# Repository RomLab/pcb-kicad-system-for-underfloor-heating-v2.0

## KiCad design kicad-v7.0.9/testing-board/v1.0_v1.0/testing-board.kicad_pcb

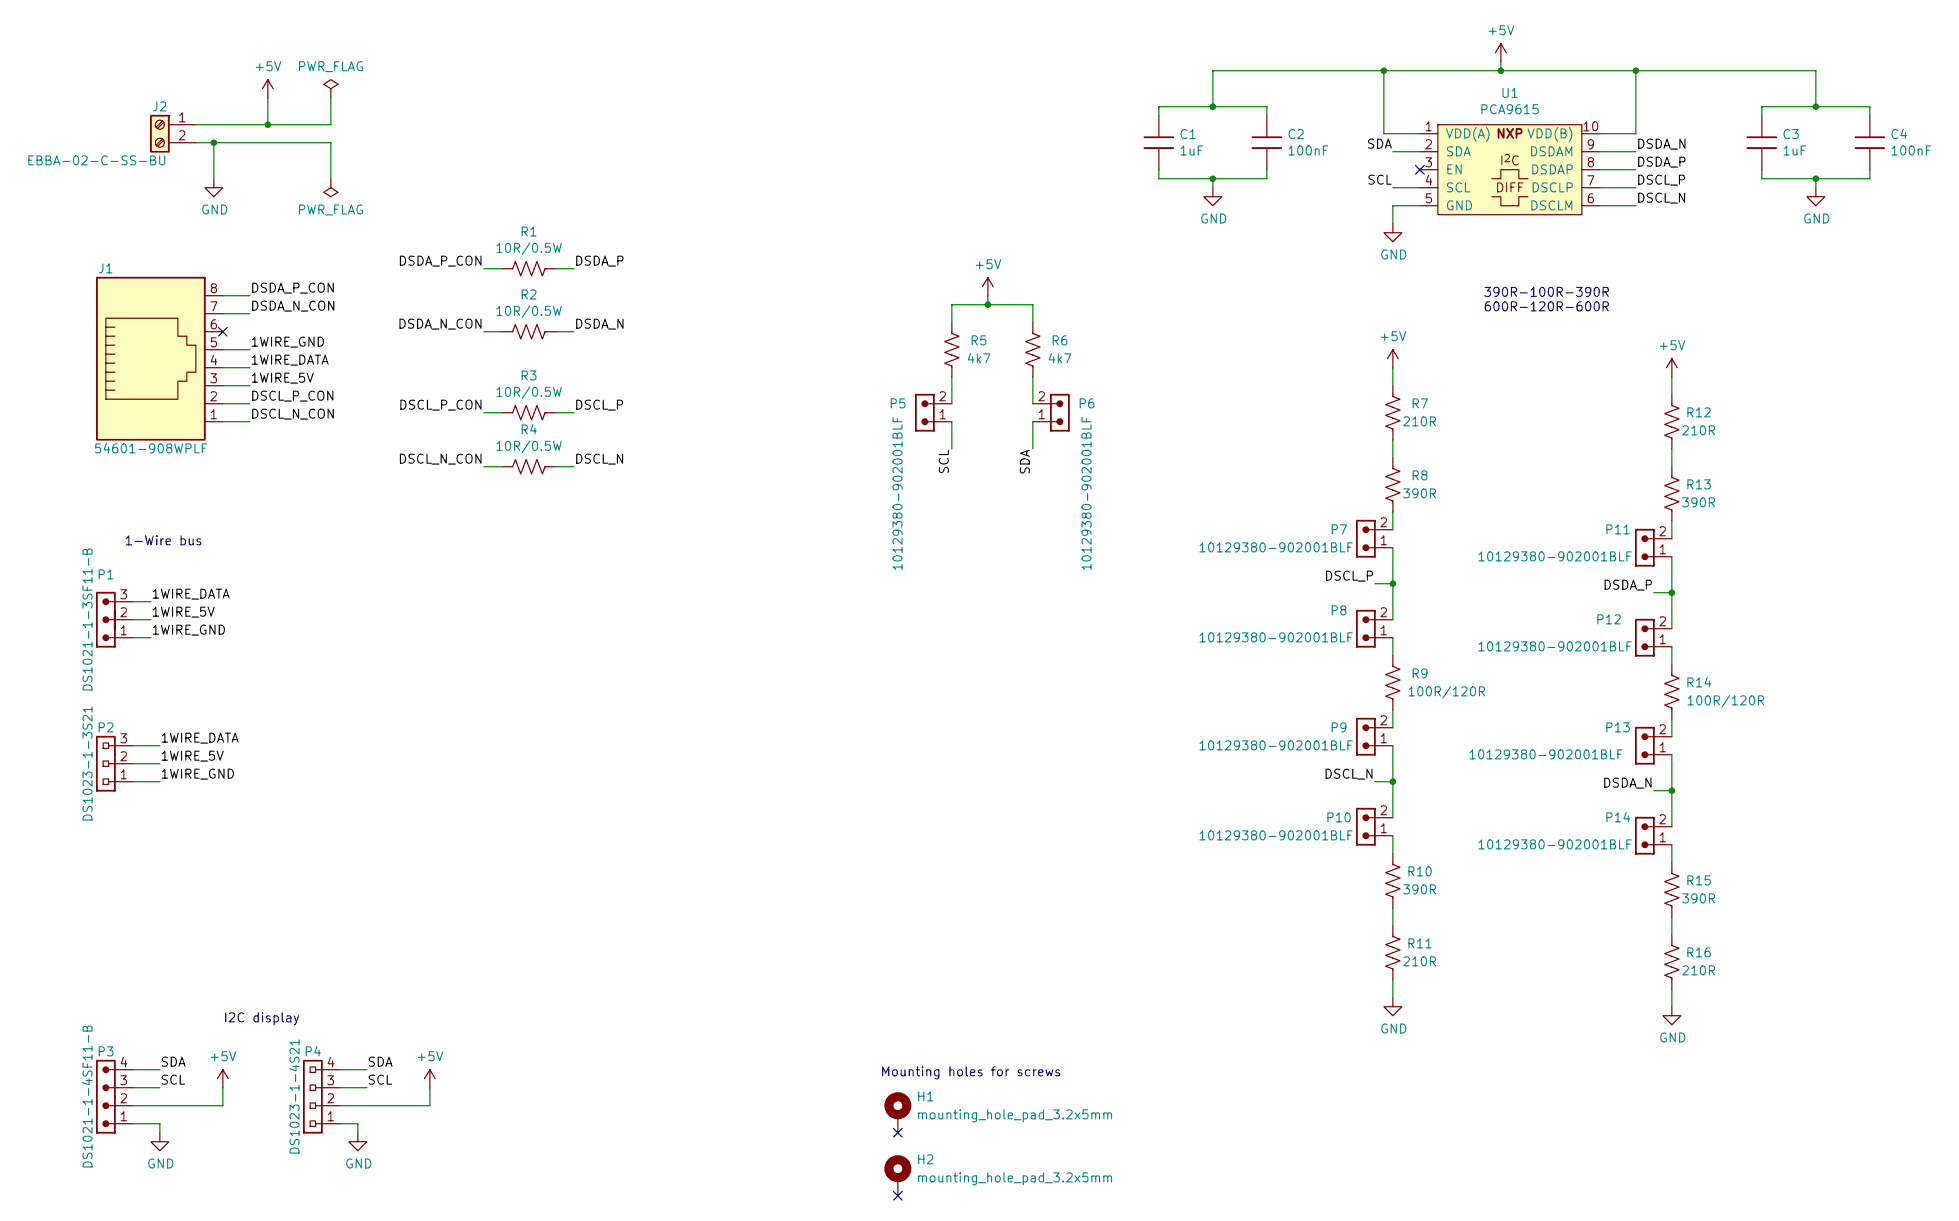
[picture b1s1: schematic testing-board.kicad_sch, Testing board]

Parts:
C1, C3: 1uF; c_1206
C2, C4: 100nF; c_1206
H1, H2: mounting_hole_pad_3.2x5mm
J1: 54601-908WPLF; rj45_54601-908WPLF
J2: EBBA-02-C-SS-BU
P1: DS1021-1-3SF11-B; 1x3_pinheader_2.54mm_vertical
P2: DS1023-1-3S21; 1x3_pinsocket_2.54mm_vertical_8.4mm
P3: DS1021-1-4SF11-B; 1x4_pinheader_2.54mm_vertical
P4: DS1023-1-4S21; 1x4_pinsocket_2.54mm_vertical_8.4mm
P5, P6, P7, P8, P9, P10, P11, P12, P13, P14: 10129380-902001BLF; 1x2_pinheader_2.54mm_vertical
R1, R2, R3, R4: 10R/0.5W; r_1206
R5, R6: 4k7; r_1206
R7, R11, R12, R16: 210R; r_1206
R8, R10, R13, R15: 390R; r_1206
R9, R14: 100R/120R; r_1206
U1: PCA9615; tssop_10

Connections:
+5V: C1.1, C2.1, C3.1, C4.1, J2.1, P3.2, P4.2, R5.1, R6.1, R7.1, R12.1, U1.1 (VDD(A)), U1.10 (VDD(B))
/1WIRE_5V: J1.3, P1.2, P2.2
/1WIRE_DATA: J1.4, P1.3, P2.3
/1WIRE_GND: J1.5, P1.1, P2.1
/DSCL_N: P9.1, P10.2, R4.2, U1.6 (DSCLM)
/DSCL_N_CON: J1.1, R4.1
/DSCL_P: P7.1, P8.2, R3.2, U1.7 (DSCLP)
/DSCL_P_CON: J1.2, R3.1
/DSDA_N: P13.1, P14.2, R2.2, U1.9 (DSDAM)
/DSDA_N_CON: J1.7, R2.1
/DSDA_P: P11.1, P12.2, R1.2, U1.8 (DSDAP)
/DSDA_P_CON: J1.8, R1.1
/SCL: P3.3, P4.3, P5.1, U1.4 (SCL)
/SDA: P3.4, P4.4, P6.1, U1.2 (SDA)
GND: C1.2, C2.2, C3.2, C4.2, J2.2, P3.1, P4.1, R11.2, R16.2, U1.5 (GND)
unnamed: P5.2, R5.2
unnamed: P6.2, R6.2
unnamed: P7.2, R8.2
unnamed: P8.1, R9.1
unnamed: P9.2, R9.2
unnamed: P10.1, R10.1
unnamed: P11.2, R13.2
unnamed: P12.1, R14.1
unnamed: P13.2, R14.2
unnamed: P14.1, R15.1
unnamed: R7.2, R8.1
unnamed: R10.2, R11.1
unnamed: R12.2, R13.1
unnamed: R15.2, R16.1

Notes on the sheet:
1-Wire bus
Mounting holes for screws
I2C display
390R-100R-390R 600R-120R-600R

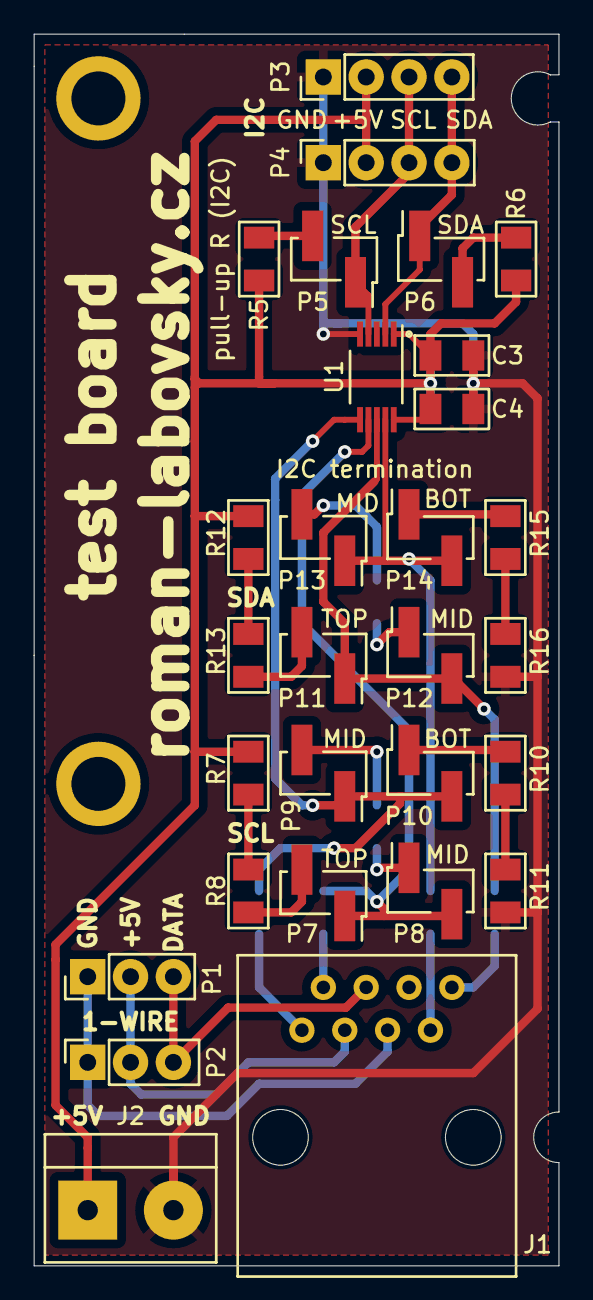
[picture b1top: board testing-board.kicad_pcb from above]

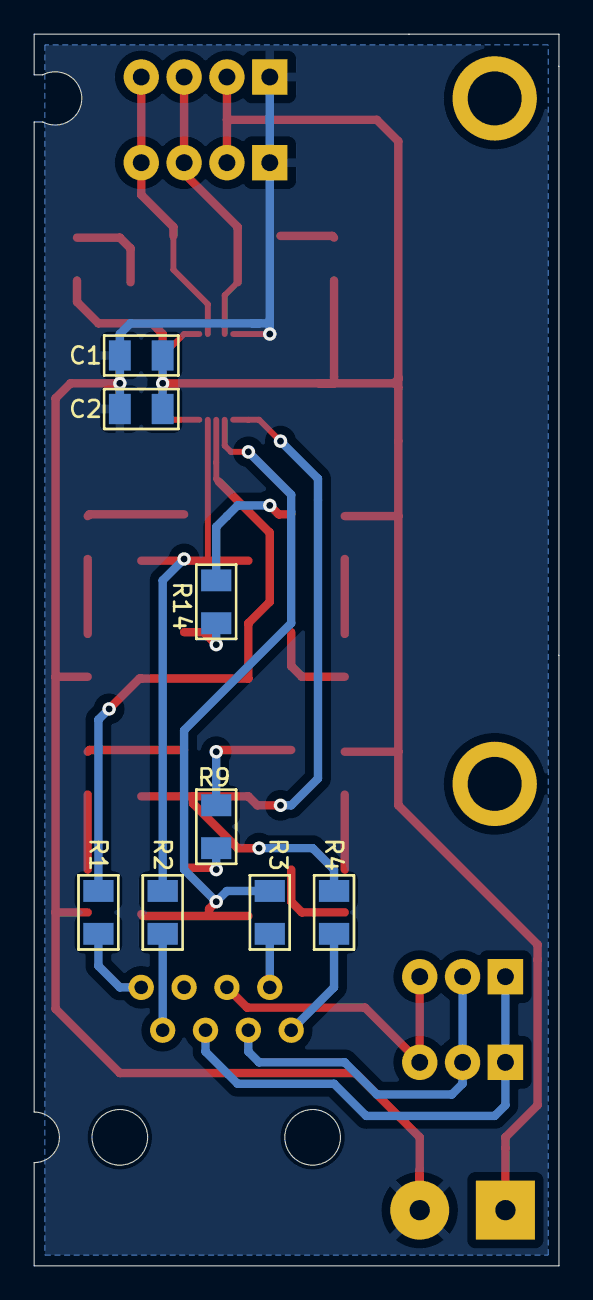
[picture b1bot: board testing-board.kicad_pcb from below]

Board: 2 copper layers, 31.1 x 73.0 mm, 39 parts (8 on the bottom side), 29 nets.

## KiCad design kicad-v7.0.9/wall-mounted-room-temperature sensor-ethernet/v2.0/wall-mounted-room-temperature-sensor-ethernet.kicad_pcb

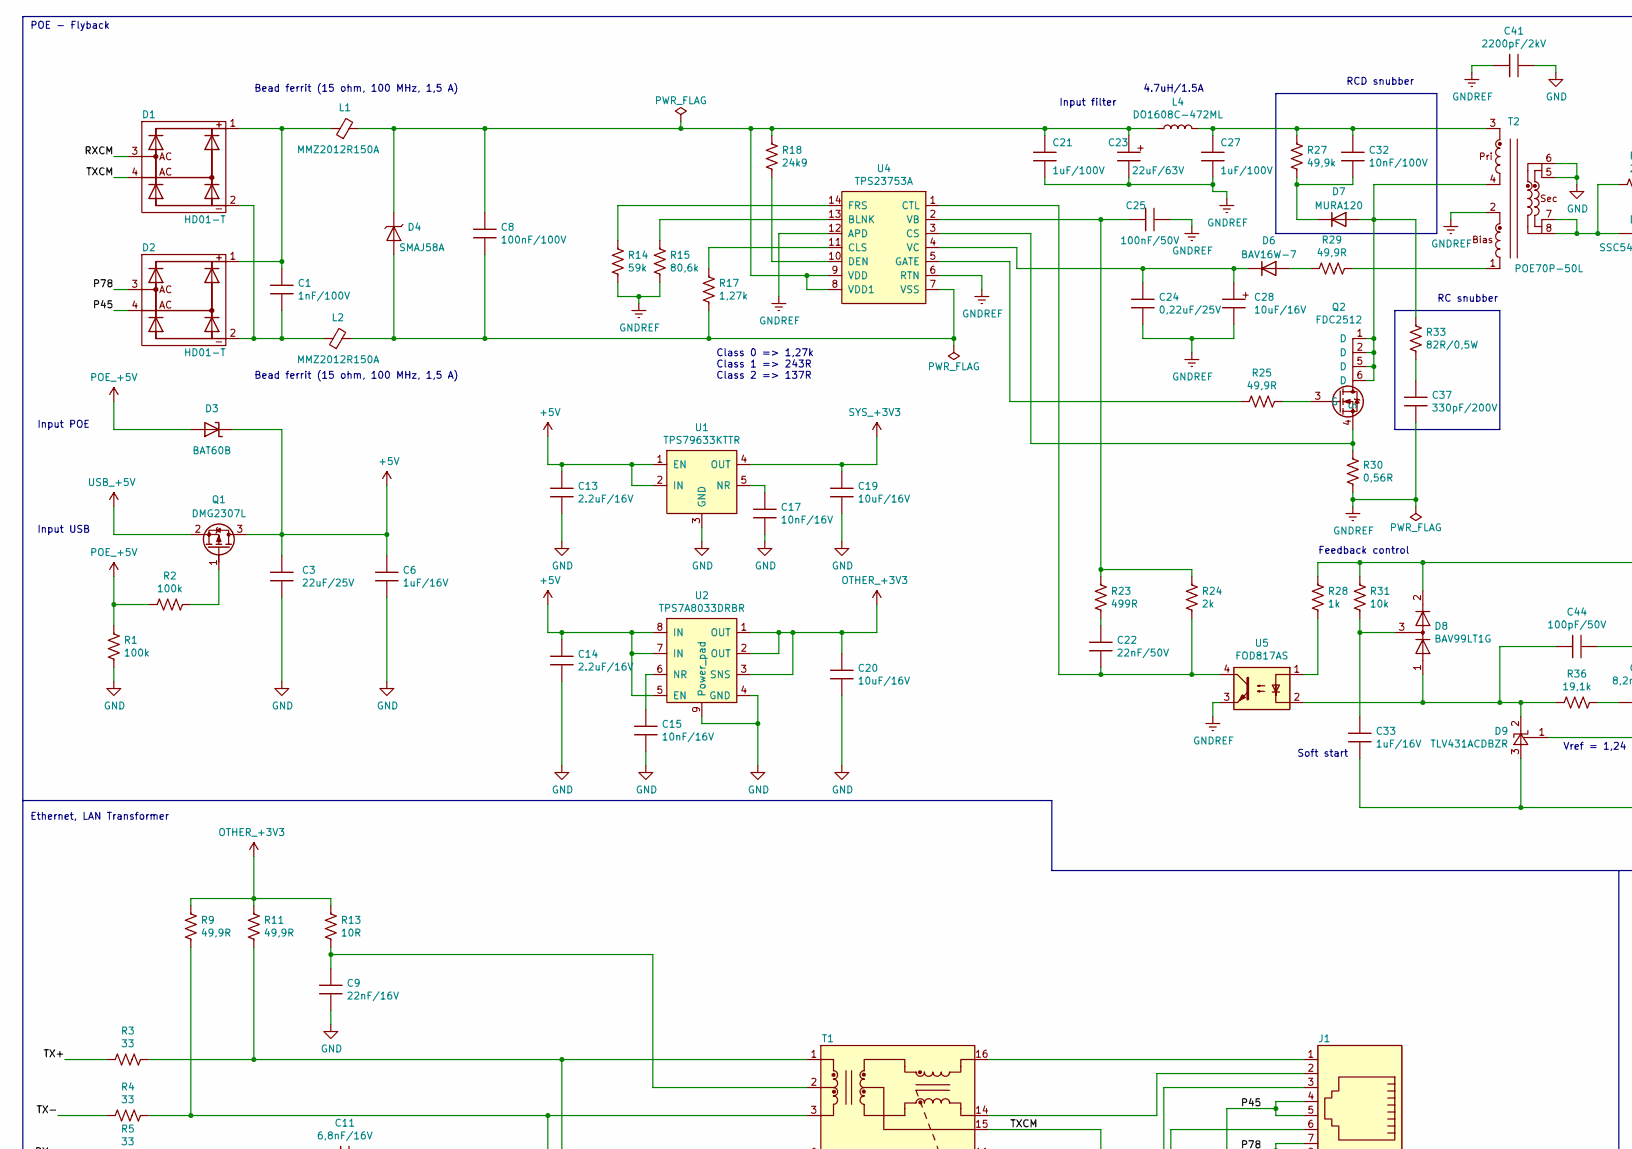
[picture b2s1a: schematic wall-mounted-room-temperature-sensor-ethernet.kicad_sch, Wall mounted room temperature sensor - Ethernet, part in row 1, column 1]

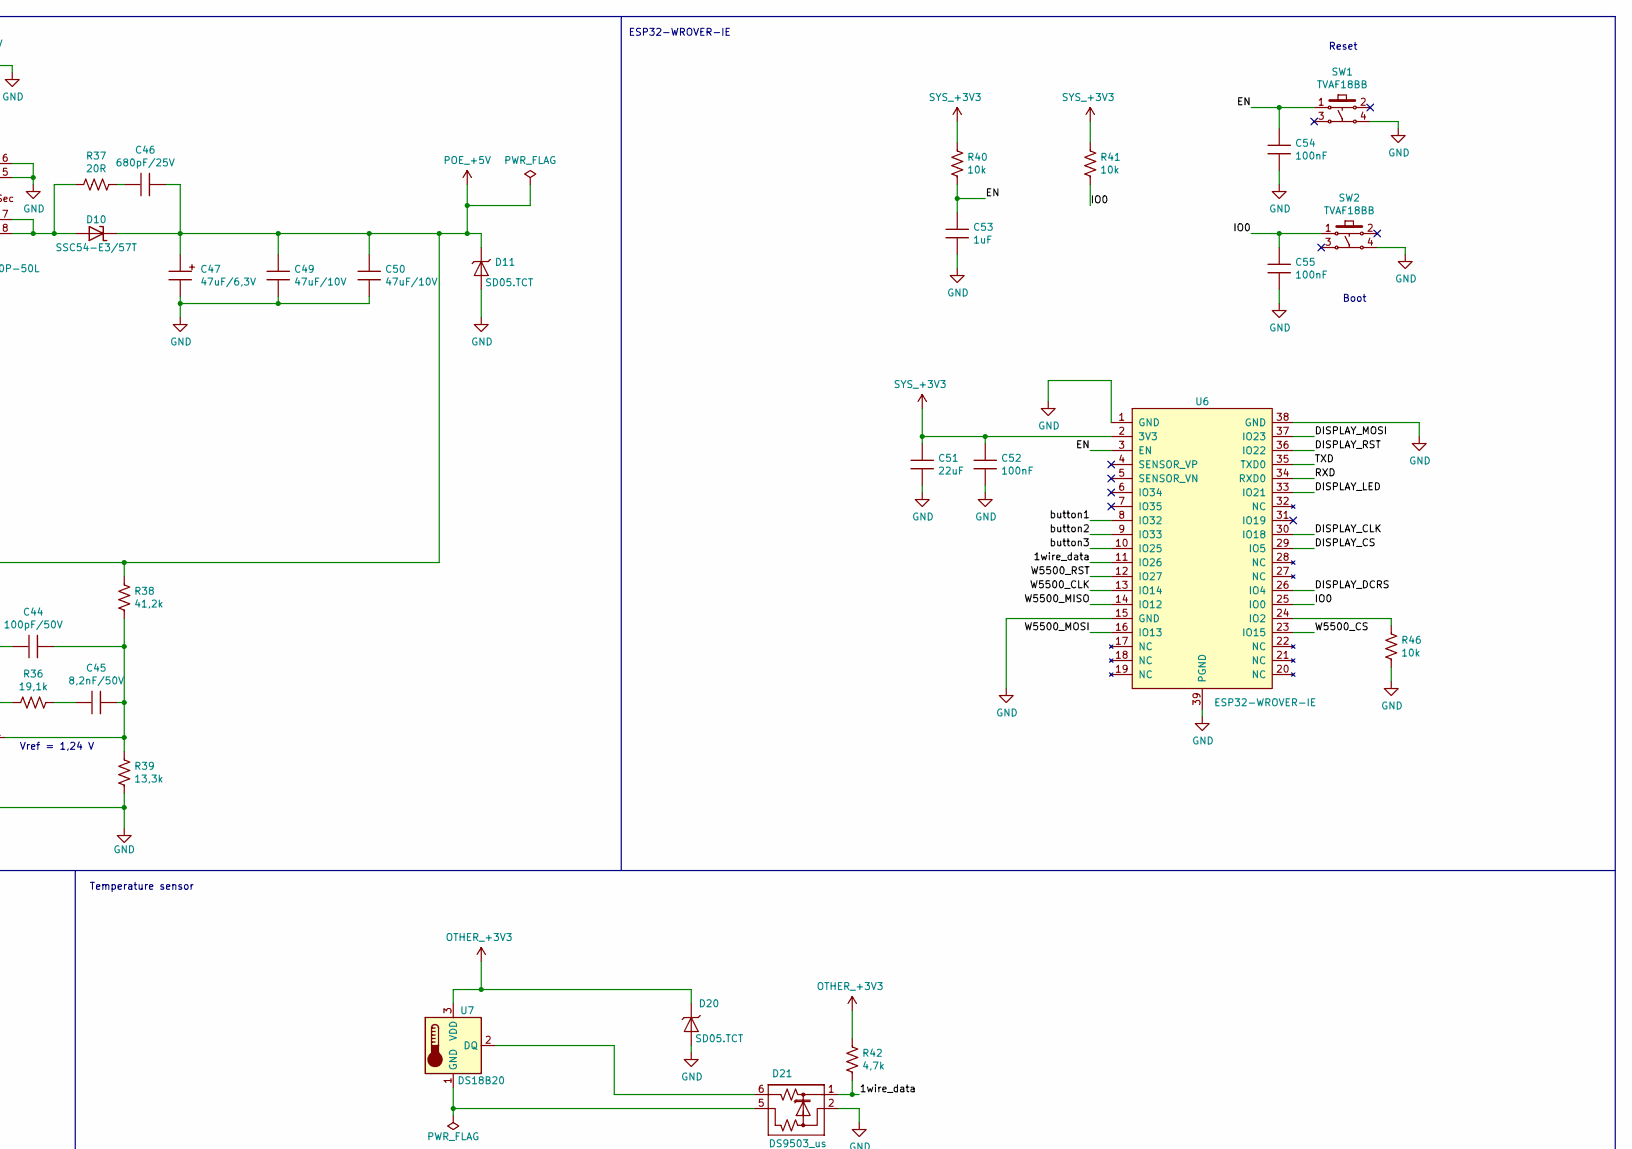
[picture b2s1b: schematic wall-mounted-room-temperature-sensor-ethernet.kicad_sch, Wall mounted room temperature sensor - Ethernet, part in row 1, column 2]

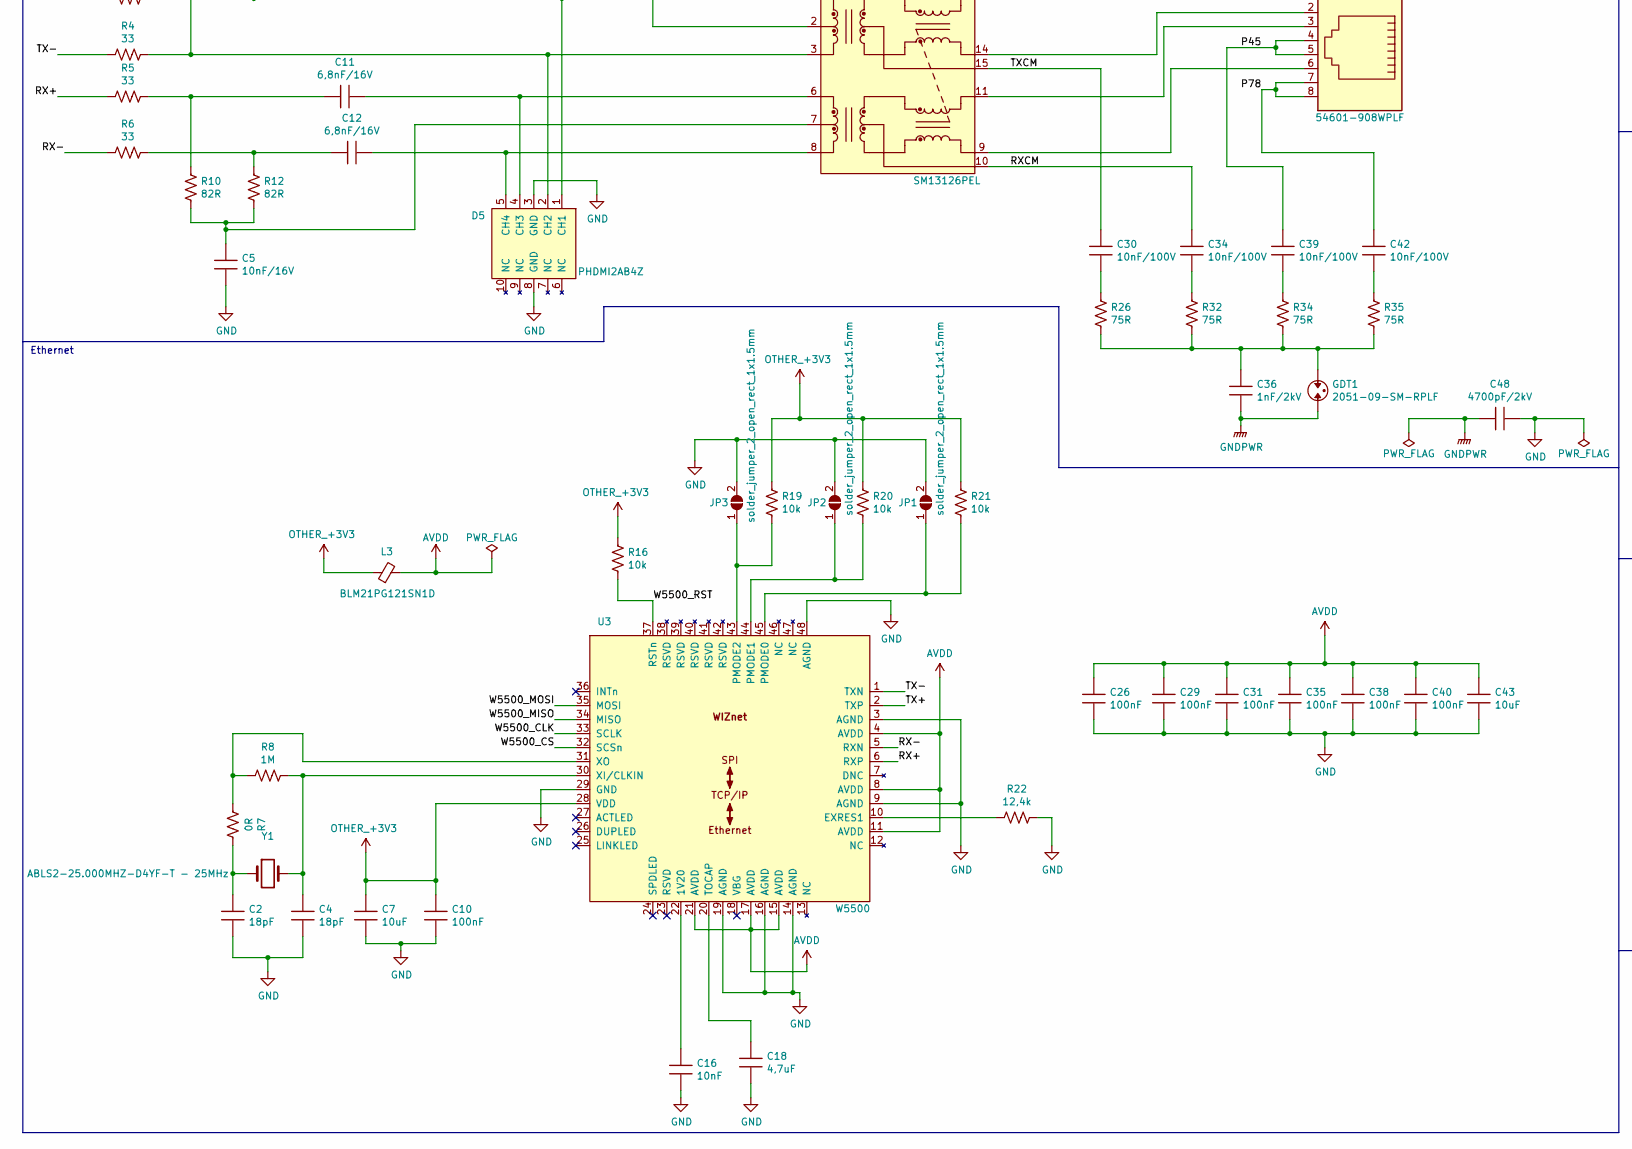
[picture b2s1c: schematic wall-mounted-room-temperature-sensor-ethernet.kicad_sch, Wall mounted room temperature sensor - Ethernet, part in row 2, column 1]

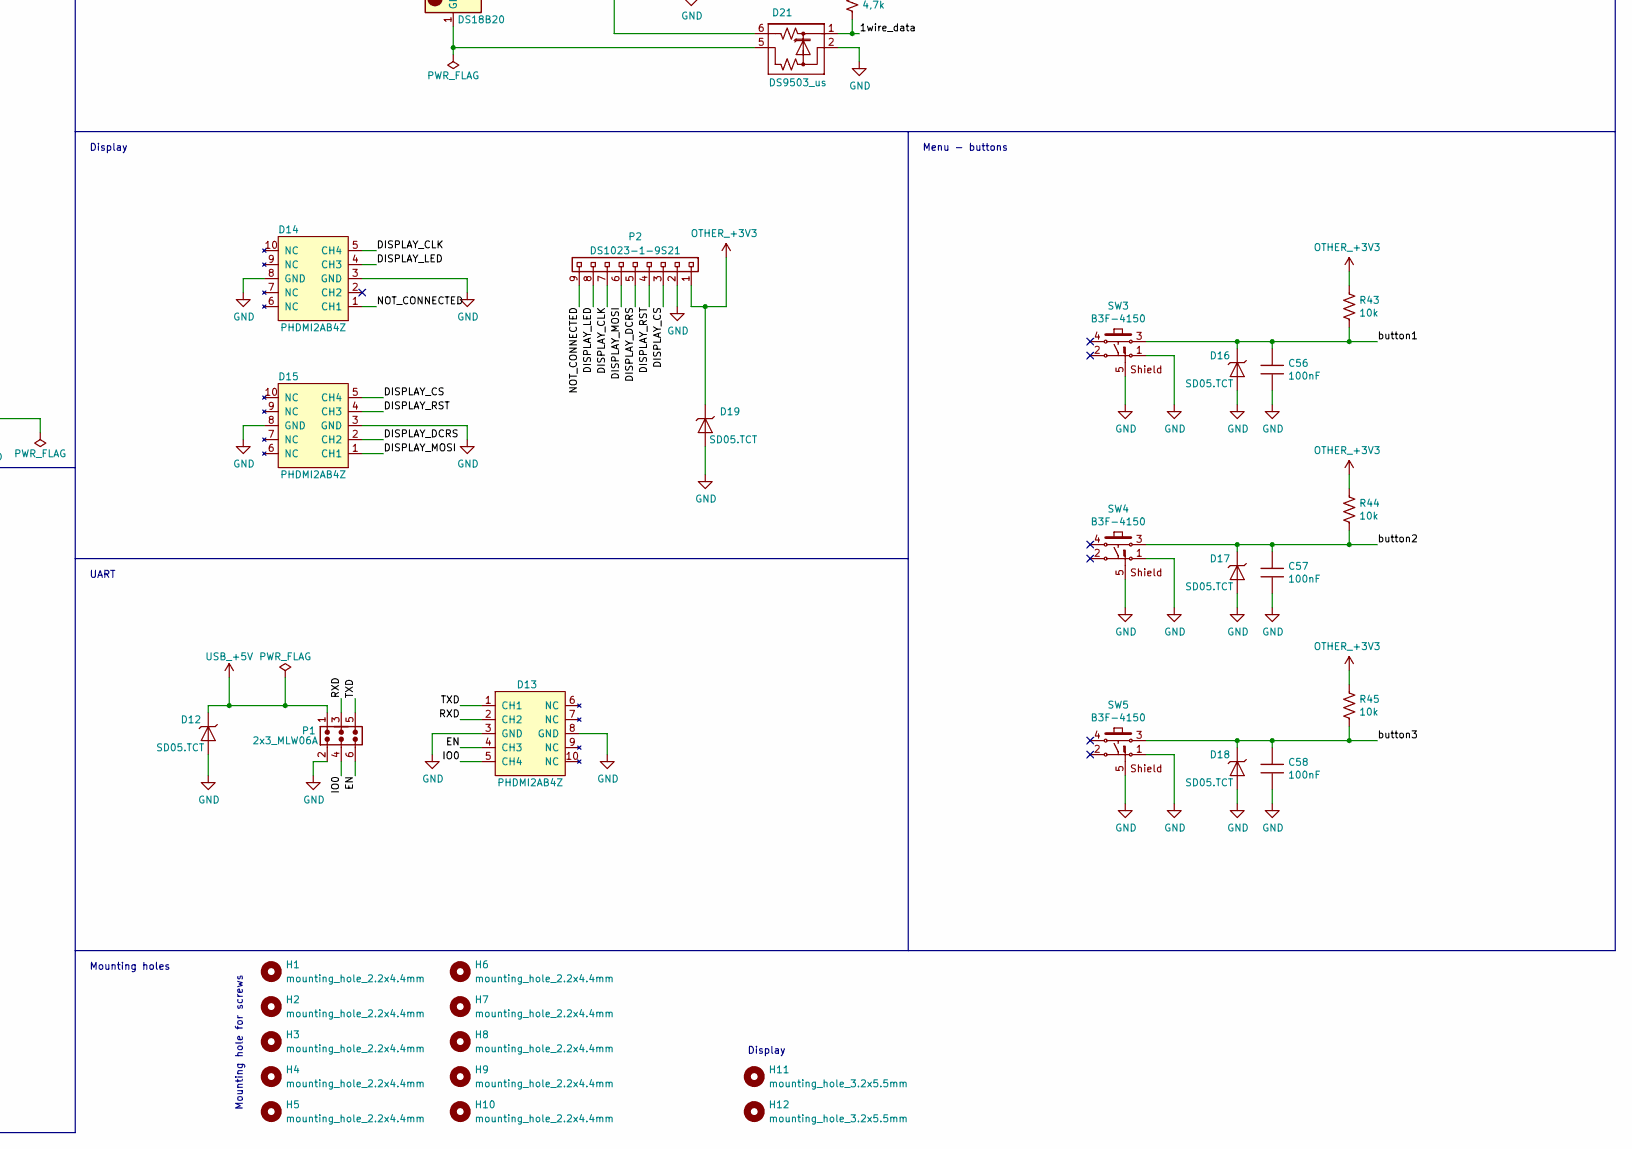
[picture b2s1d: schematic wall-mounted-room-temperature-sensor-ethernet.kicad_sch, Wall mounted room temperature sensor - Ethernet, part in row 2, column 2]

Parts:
C1: 1nF/100V; c_0805
C2, C4: 18pF; c_0805
C3: 22uF/25V; c_0805
C5, C15, C17: 10nF/16V; c_0805
C6, C33: 1uF/16V; c_0805
C7, C43: 10uF; c_0805
C8: 100nF/100V; c_0805
C9: 22nF/16V; c_0805
C10, C26, C29, C31, C35, C38, C40, C52, C54, C55, C56, C57, C58: 100nF; c_0805
C11, C12: 6,8nF/16V; c_0805
C13, C14: 2.2uF/16V; c_0805
C16: 10nF; c_0805
C18: 4,7uF; c_0805
C19, C20: 10uF/16V; c_0805
C21, C27: 1uF/100V; c_1206
C22: 22nF/50V; c_0805
C23: 22uF/63V; c_elec_6.3x7.7
C24: 0,22uF/25V; c_0805
C25: 100nF/50V; c_0805
C28: 10uF/16V; c_elec_4x5.8
C30, C32, C34, C39, C42: 10nF/100V; c_0805
C36: 1nF/2kV; c_1206
C37: 330pF/200V; c_0805
C41: 2200pF/2kV; c_1812
C44: 100pF/50V; c_0805
C45: 8,2nF/50V; c_0805
C46: 680pF/25V; c_0805
C47: 47uF/6,3V; c_elec_4x5.8
C48: 4700pF/2kV; c_1812
C49, C50: 47uF/10V; c_0805
C51: 22uF; c_0805
C53: 1uF; c_0805
D1, D2: HD01-T; mini_dip
D3: BAT60B; sod_323
D4: SMAJ58A; do_214ac
D5, D13, D14, D15: PHDMI2AB4Z; dfn_2510a_10
D6: BAV16W-7; sod_123
D7: MURA120; sma
D8: BAV99LT1G; sot_23_3
D9: TLV431ACDBZR; sot_23_3
D10: SSC54-E3/57T; smc_do_214ab
D11, D12, D16, D17, D18, D19, D20: SD05.TCT; sod_323
D21: DS9503_us; tsoc_6
GDT1: 2051-09-SM-RPLF
H1, H2, H3, H4, H5, H6, H7, H8, H9, H10: mounting_hole_2.2x4.4mm
H11, H12: mounting_hole_3.2x5.5mm
J1: 54601-908WPLF; rj45_54601-908WPLF
JP1, JP2, JP3: solder_jumper_2_open_rect_1x1.5mm
L1, L2: MMZ2012R150A; ferrite_bead_0805
L3: BLM21PG121SN1D; ferrite_bead_0805
L4: DO1608C-472ML
P1: 2x3_MLW06A
P2: DS1023-1-9S21; 1x9_pinsocket_2.54mm_vertical_8.4mm
Q1: DMG2307L; sot_23_3
Q2: FDC2512; tsot_23_6
R1, R2: 100k; r_0805
R3, R4, R5, R6: 33; r_0805
R7: 0R; r_0805
R8: 1M; r_0805
R9, R11, R25, R29: 49,9R; r_0805
R10, R12: 82R; r_1206
R13: 10R; r_0805
R14: 59k; r_0805
R15: 80,6k; r_0805
R16, R19, R20, R21, R31, R40, R41, R43, R44, R45, R46: 10k; r_0805
R17: 1,27k; r_0805
R18: 24k9; r_0805
R22: 12,4k; r_0805
R23: 499R; r_0805
R24: 2k; r_0805
R26, R32, R34, R35: 75R; r_0805
R27: 49,9k; r_0805
R28: 1k; r_0805
R30: 0,56R; r_1206
R33: 82R/0,5W; r_1206
R36: 19,1k; r_0805
R37: 20R; r_0805
R38: 41,2k; r_0805
R39: 13,3k; r_0805
R42: 4,7k; r_0805
SW1, SW2: TVAF18BB
SW3, SW4, SW5: B3F-4150
T1: SM13126PEL
T2: POE70P-50L
U1: TPS79633KTTR; to_263_5
U2: TPS7A8033DRBR; son_8
U3: W5500; lqfp_48
U4: TPS23753A; tssop_14
U5: FOD817AS; dip_4
U6: ESP32-WROVER-IE
U7: DS18B20; to_92_in_line
Y1: ABLS2-25.000MHZ-D4YF-T - 25MHz; ABLS2-25.000MHZ-D4YF-T

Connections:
+5V: C3.1, C6.1, C13.1, C14.1, D3.1 (K), Q1.3 (D), U1.1 (EN), U1.2 (IN), U2.5 (EN), U2.7 (IN), U2.8 (IN)
/1wire_data: D21.1 (K), R42.2, U6.11 (IO26)
/DISPLAY_CLK: D14.5 (CH4), P2.7, U6.30 (IO18)
/DISPLAY_CS: D15.5 (CH4), P2.3, U6.29 (IO5)
/DISPLAY_DCRS: D15.2 (CH2), P2.5, U6.26 (IO4)
/DISPLAY_LED: D14.4 (CH3), P2.8, U6.33 (IO21)
/DISPLAY_MOSI: D15.1 (CH1), P2.6, U6.37 (IO23)
/DISPLAY_RST: D15.4 (CH3), P2.4, U6.36 (IO22)
/EN: C53.1, C54.1, D13.4 (CH3), P1.6, R40.2, SW1.1, U6.3 (EN)
/IO0: C55.1, D13.5 (CH4), P1.4, R41.2, SW2.1, U6.25 (IO0)
/NOT_CONNECTED: D14.1 (CH1), P2.9
/P45: C39.1, D2.4, J1.4, J1.5
/P78: C42.1, D2.3, J1.7, J1.8
/RX+: R5.1, U3.6 (RXP)
/RX-: R6.1, U3.5 (RXN)
/RXCM: C34.1, D1.3, T1.10
/RXD: D13.2 (CH2), P1.3, U6.34 (RXD0)
/TX+: R3.1, U3.2 (TXP)
/TX-: R4.1, U3.1 (TXN)
/TXCM: C30.1, D1.4, T1.15
/TXD: D13.1 (CH1), P1.5, U6.35 (TXD0)
/W5500_CLK: U3.33 (SCLK), U6.13 (IO14)
/W5500_CS: U3.32 (SCSn), U6.23 (IO15)
/W5500_MISO: U3.34 (MISO), U6.14 (IO12)
/W5500_MOSI: U3.35 (MOSI), U6.16 (IO13)
/W5500_RST: R16.2, U3.37 (RSTn), U6.12 (IO27)
/button1: C56.1, D16.1 (K), R43.2, SW3.3, U6.8 (IO32)
/button2: C57.1, D17.1 (K), R44.2, SW4.3, U6.9 (IO33)
/button3: C58.1, D18.1 (K), R45.2, SW5.3, U6.10 (IO25)
AVDD: C26.1, C29.1, C31.1, C35.1, C38.1, C40.1, C43.1, L3.2, U3.4 (AVDD), U3.8 (AVDD), U3.11 (AVDD), U3.15 (AVDD), U3.17 (AVDD), U3.21 (AVDD)
GND: C2.2, C3.2, C4.2, C5.2, C6.2, C7.2, C9.2, C10.2, C13.2, C14.2, C15.2, C16.2, C17.2, C18.2, C19.2, C20.2, C26.2, C29.2, C31.2, C33.2, C35.2, C38.2, C40.2, C41.2, C43.2, C47.2, C48.2, C49.1, C50.2, C51.2, C52.2, C53.2, C54.2, C55.2, C56.2, C57.2, C58.2, D5.3 (GND), D5.8 (GND), D9.3 (A), D11.2 (A), D12.2 (A), D13.3 (GND), D13.8 (GND), D14.3 (GND), D14.8 (GND), D15.3 (GND), D15.8 (GND), D16.2 (A), D17.2 (A), D18.2 (A), D19.2 (A), D20.2 (A), D21.2 (A), JP1.2 (B), JP2.2 (B), JP3.2 (B), P1.2, P2.2, R1.2, R22.2, R39.2, R46.2, SW1.4, SW2.4, SW3.1, SW3.5 (GND), SW4.1, SW4.5 (GND), SW5.1, SW5.5 (GND), T2.5, T2.6, U1.3 (GND), U2.4 (GND), U2.9 (Power_pad), U3.3 (AGND), U3.9 (AGND), U3.14 (AGND), U3.16 (AGND), U3.19 (AGND), U3.29 (GND), U3.48 (AGND), U6.1 (GND), U6.15 (GND), U6.38 (GND), U6.39 (PGND)
GNDPWR: C36.2, C48.1, GDT1.2
GNDREF: C21.2, C23.2, C24.2, C25.2, C27.2, C28.2, C37.2, C41.1, R14.2, R15.2, R30.2, T2.2, U4.6 (RTN), U4.12 (APD), U5.3
unnamed: C1.1, D1.1, D2.1, L1.1
unnamed: C1.2, D1.2, D2.2, L2.1
unnamed: C2.1, R7.2, Y1.1
unnamed: C5.1, R10.2, R12.2, T1.7
unnamed: C9.1, R13.2, T1.2
unnamed: C11.1, R5.2, R10.1
unnamed: C12.1, R6.2, R12.1
unnamed: C22.1, R23.2
unnamed: C27.1, C32.1, L4.2, R27.1, T2.3
unnamed: C30.2, R26.1
unnamed: C33.1, D8.3 (K), R31.2
unnamed: C34.2, R32.1
unnamed: C36.1, GDT1.1, R26.2, R32.2, R34.2, R35.2
unnamed: C37.1, R33.2
unnamed: C39.2, R34.1
unnamed: C42.2, R35.1
unnamed: C45.1, R36.2
unnamed: C46.1, R37.2
unnamed: C8.2, D4.2 (A), L2.2, R17.2, U4.7 (VSS)
unnamed: C8.1, C21.1, C23.1, D4.1 (K), L1.2, L4.1, R18.1, U4.8 (VDD1), U4.9 (VDD)
unnamed: D5.1 (CH1), R3.2, R11.2, T1.1
unnamed: D5.2 (CH2), R4.2, R9.2, T1.3
unnamed: C11.2, D5.4 (CH3), T1.6
unnamed: C12.2, D5.5 (CH4), T1.8
unnamed: D6.2 (A), R29.1
unnamed: C24.1, C28.1, D6.1 (K), U4.4 (VC)
unnamed: D7.2 (A), Q2.1 (D), Q2.2 (D), Q2.5 (D), Q2.6 (D), R33.1, T2.4
unnamed: C32.2, D7.1 (K), R27.2
unnamed: C44.2, C45.2, D9.1 (FB), R38.2, R39.1
unnamed: C44.1, D8.1 (K), D9.2 (K), R36.1, U5.2
unnamed: D10.2 (A), R37.1, T2.7, T2.8
unnamed: J1.1, T1.16
unnamed: J1.2, T1.14
unnamed: J1.3, T1.11
unnamed: J1.6, T1.9
unnamed: JP1.1 (A), R21.2, U3.45 (PMODE0)
unnamed: JP2.1 (A), R20.2, U3.44 (PMODE1)
unnamed: JP3.1 (A), R19.2, U3.43 (PMODE2)
unnamed: Q1.1 (G), R2.2
unnamed: Q2.3 (G), R25.2
unnamed: Q2.4 (S), R30.1, U4.3 (CS)
unnamed: R28.2, U5.1
unnamed: R29.2, T2.1
unnamed: C17.1, U1.5 (NR)
unnamed: C15.1, U2.6 (NR)
unnamed: C16.1, U3.22 (1V20)
unnamed: R22.1, U3.10 (EXRES1)
unnamed: C18.1, U3.20 (TOCAP)
unnamed: C4.1, R8.2, U3.30 (XI/CLKIN), Y1.2
unnamed: R7.1, R8.1, U3.31 (XO)
unnamed: R15.1, U4.13 (BLNK)
unnamed: R17.1, U4.11 (CLS)
unnamed: C22.2, R24.2, U4.1 (CTL), U5.4
unnamed: R18.2, U4.10 (DEN)
unnamed: R14.1, U4.14 (FRS)
unnamed: R25.1, U4.5 (GATE)
unnamed: C25.1, R23.1, R24.1, U4.2 (VB)
unnamed: R46.1, U6.24 (IO2)
unnamed: D21.6 (K), U7.2 (DQ)
unnamed: D21.5 (A), U7.1 (GND)
OTHER_+3V3: C7.1, C10.1, C20.1, D19.1 (K), D20.1 (K), L3.1, P2.1, R9.1, R11.1, R13.1, R16.1, R19.1, R20.1, R21.1, R42.1, R43.1, R44.1, R45.1, U2.1 (OUT), U2.2 (OUT), U2.3 (SNS), U3.28 (VDD), U7.3 (VDD)
POE_+5V: C46.2, C47.1, C49.2, C50.1, D3.2 (A), D8.2 (A), D10.1 (K), D11.1 (K), R1.1, R2.1, R28.1, R31.1, R38.1
SYS_+3V3: C19.1, C51.1, C52.1, R40.1, R41.1, U1.4 (OUT), U6.2 (3V3)
USB_+5V: D12.1 (K), P1.1, Q1.2 (S)

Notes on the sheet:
Class 0 => 1,27k Class 1 => 243R Class 2 => 137R
Bead ferrit (15 ohm, 100 MHz, 1,5 A)
POE - Flyback
4.7uH/1.5A
Feedback control
Display
RC snubber
Soft start
Menu - buttons
Mounting holes
UART
Mounting hole for screws
ESP32-WROVER-IE
Boot
Ethernet, LAN Transformer
Vref = 1,24 V
RCD snubber
Input POE
Temperature sensor
Reset
Ethernet
Input USB
Input filter

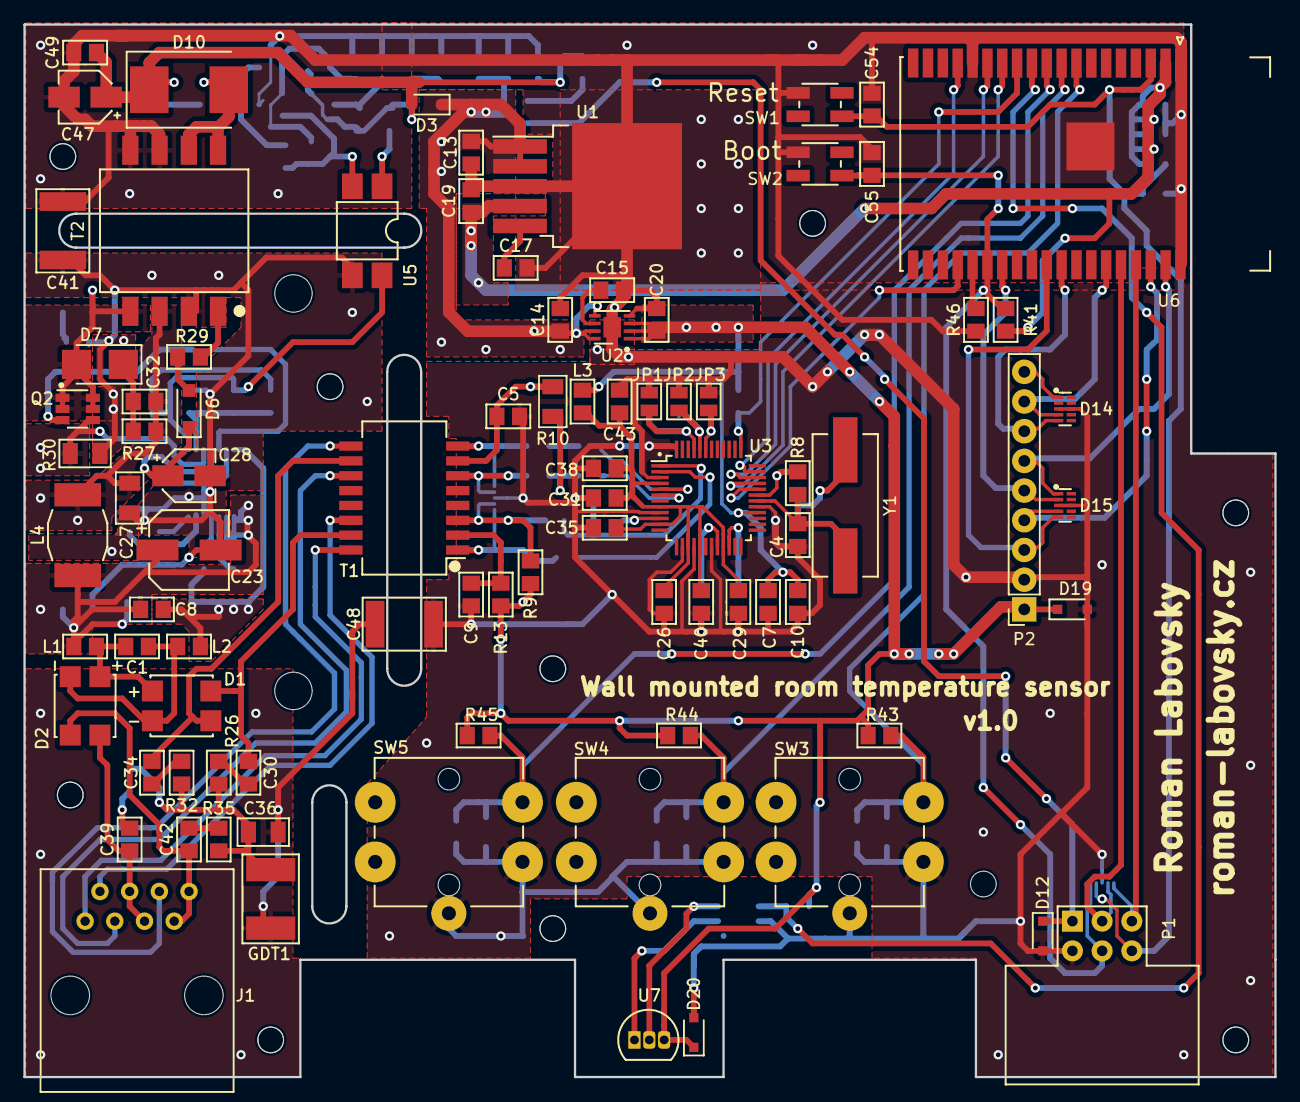
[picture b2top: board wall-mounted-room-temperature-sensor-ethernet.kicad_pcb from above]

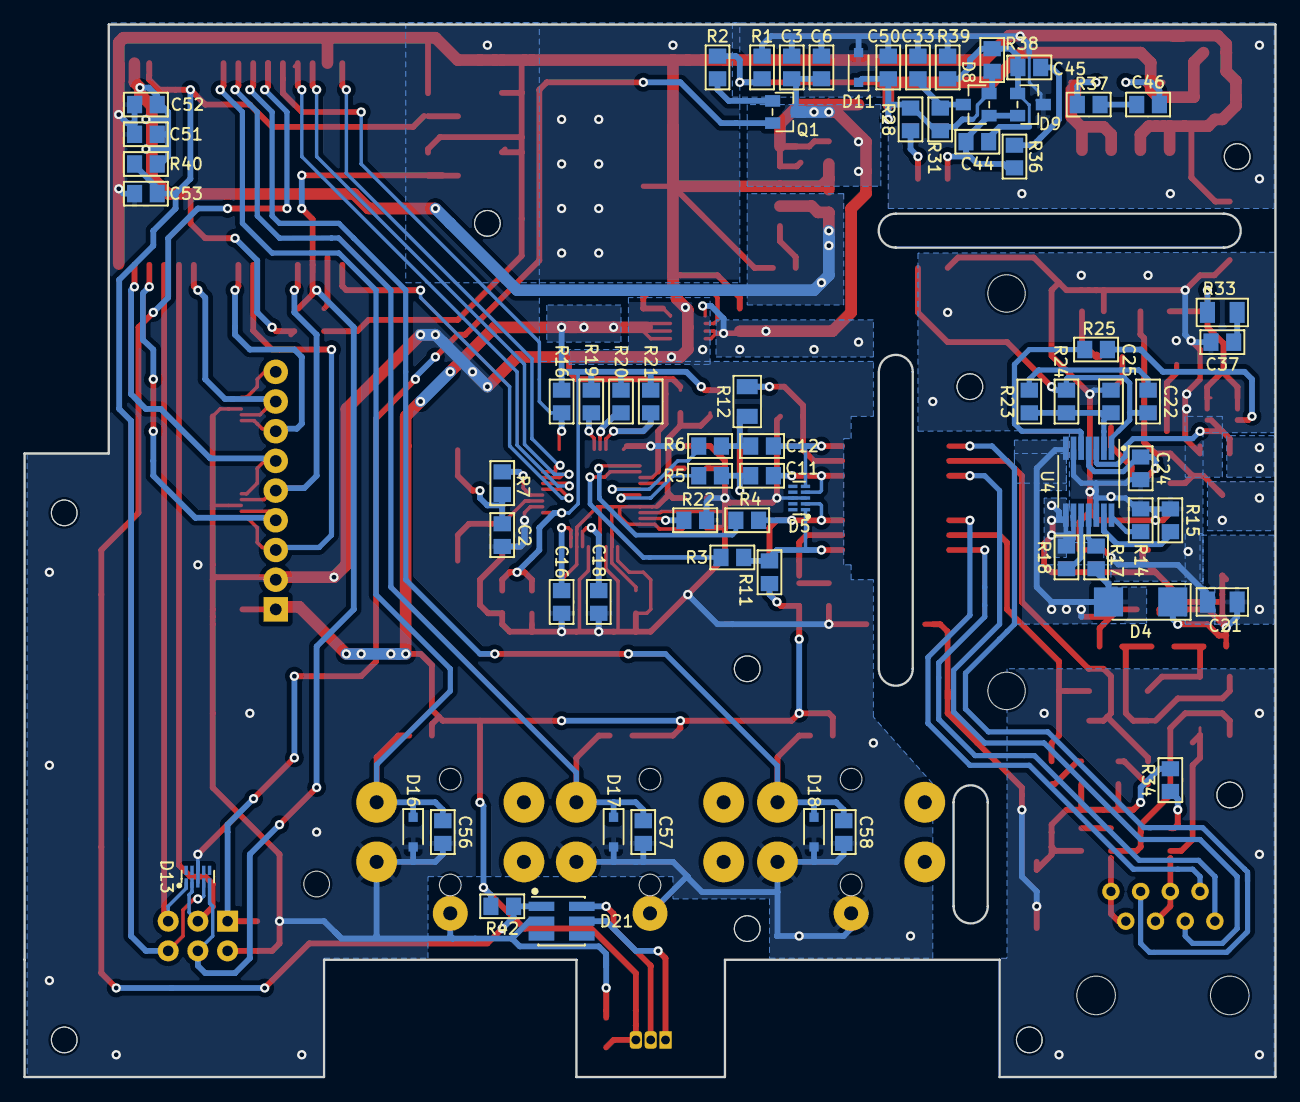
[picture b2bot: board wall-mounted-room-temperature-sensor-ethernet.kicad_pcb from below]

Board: 2 copper layers, 107.0 x 90.0 mm, 165 parts (66 on the bottom side), 97 nets.
